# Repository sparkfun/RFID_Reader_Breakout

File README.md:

RFID Reader Breakout
==================

[  
*RFID Reader Breakout (SEN-13030)*](https://www.sparkfun.com/products/13030)

The RFID Reader Breakout converts the 2mm pins to bread board friendly 0.1" headers. Solder the module directly to the breakout board or use the [2mm connectors](https://www.sparkfun.com/products/8272) for a socketed solution.

Repository Contents
-------------------
* **/Hardware** - All Eagle design files (.brd, .sch)

Version History
---------------
* [SEN-08423](https://www.sparkfun.com/products/retired/8423) Retired version of the RFID Reader Breakout

License Information
-------------------
The hardware is released under [Creative Commons ShareAlike 4.0 International](https://creativecommons.org/licenses/by-sa/4.0/).

Distributed as-is; no warranty is given.

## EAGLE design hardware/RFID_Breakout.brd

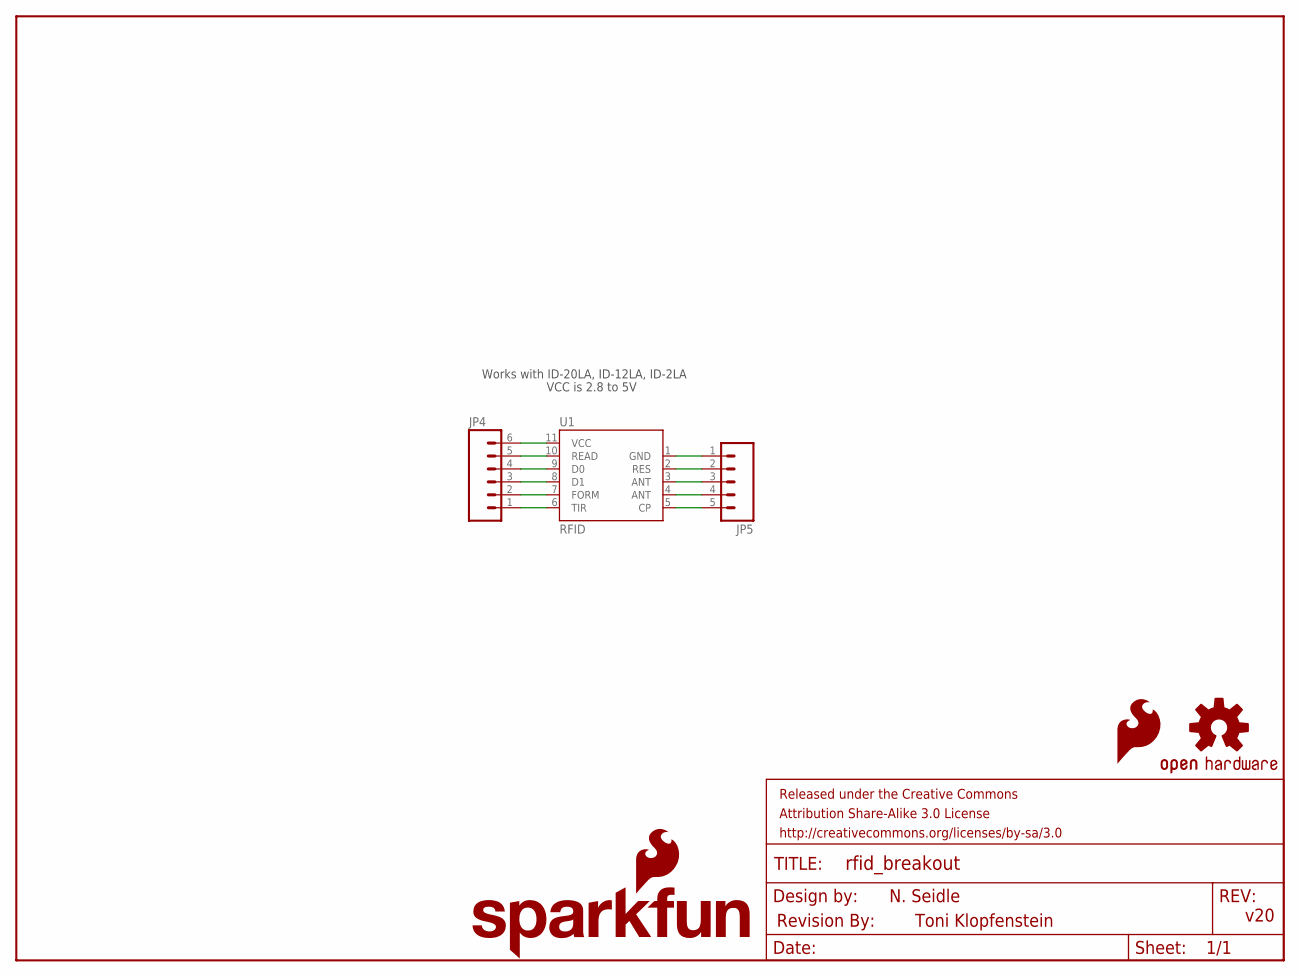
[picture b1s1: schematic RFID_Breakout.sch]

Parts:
FRAME1: FRAME-LETTER; CREATIVE_COMMONS
JP4: M06SIP; 1X06
JP5: M05PTH; 1X05
LOGO1: SFE_LOGO_FLAME.1_INCH; SFE_LOGO_FLAME_.1
LOGO2: SFE_LOGO_NAME_FLAME.1_INCH; SFE_LOGO_NAME_FLAME_.1
LOGO3: OSHW-LOGOS; OSHW-LOGO-S
U1: RFID; ID_PACKAGE
U$1: REVISION

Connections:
ANT1: JP5.3, U1.3 (ANT)
ANT2: JP5.4, U1.4 (ANT)
CP: JP5.5, U1.5 (CP)
D0: JP4.4, U1.9 (D0)
D1: JP4.3, U1.8 (D1)
FORM: JP4.2, U1.7 (FORM)
unnamed: JP4.6, U1.11 (VCC)
unnamed: JP5.1, U1.1 (GND)
READ: JP4.5, U1.10 (READ)
RES: JP5.2, U1.2 (RES)
TIR: JP4.1, U1.6 (TIR)

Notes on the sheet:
VCC is 2.8 to 5V
v20
N. Seidle
Works with ID-20LA, ID-12LA, ID-2LA
Toni Klopfenstein

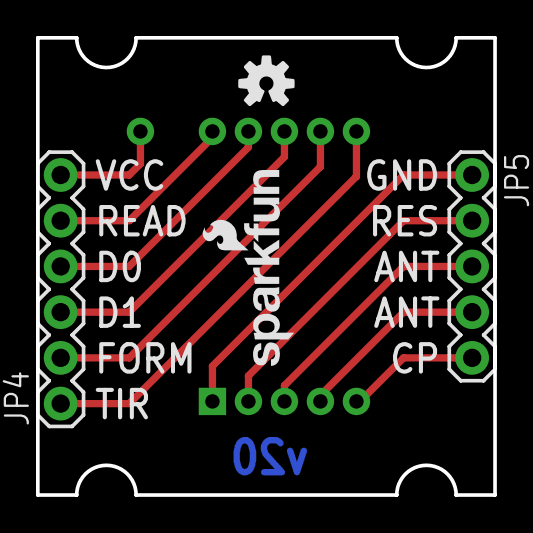
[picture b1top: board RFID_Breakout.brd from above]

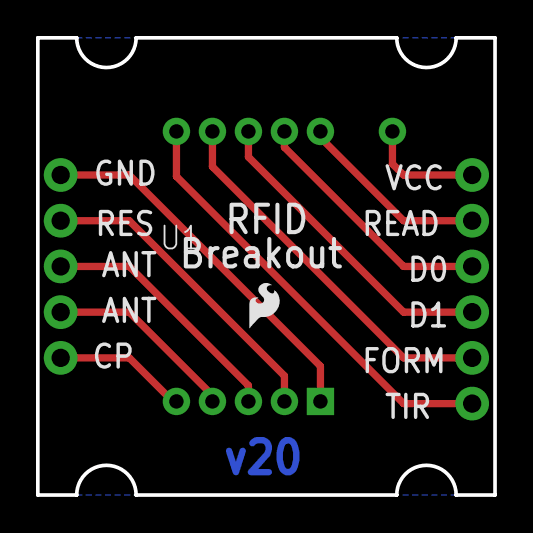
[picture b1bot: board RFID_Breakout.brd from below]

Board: 2 copper layers, 25.4 x 25.4 mm, 8 parts (2 on the bottom side), 11 nets.

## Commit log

2014-01-09 Adding readme and moving files around.
2014-01-09 Added schematic. Improved footprint.
    Footprint includes outer dimensions for the three sizes of readers.
2014-01-09 Corrected layout to work with breadboard.
2014-01-22 Reversed layout to make labels visible when attached.
2014-01-22 Added version v20 to bottom copper.
2014-07-16 Updating silkscreen to both sides, adding in OSHW logo, adding in bottom copper for version number
2014-07-16 Fixing isolate and upping trace widths
2014-08-07 Updating README with new part information

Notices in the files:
parts and their libraries:
SparkFun-Aesthetics: Licensing: CC v3.0 Share-Alike You are welcome to use this library for commercial purposes.
SparkFun-Aesthetics: Released under the Creative Commons Attribution Share-Alike 3.0 License
SparkFun-Aesthetics: http://creativecommons.org/licenses/by-sa/3.0
